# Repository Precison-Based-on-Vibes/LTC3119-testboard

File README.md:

# LTC3119-testboard
LTC3119 testbord is a device build to test MPPT adaptation of this DCDC converter

## Schematic

## Tests Documentation

### Configuration A
- Configuration of a testbed before tests:
    - Input Capacitance: 4 x 22 uF
    - Output Capacitance: 4 x 22uF
    - MPPC Compensation: 10nF, 1k47 Ohm (C5, R5)
    - Evrything else: same as in design files

- Nominal operation - Output noice mesurment (probed directly with coaxial cable with 50 ohm terminantion on oscilosope)
    - No external load (PSU not current limited)  
    
    - External load 1A (PSU not current limited)  
    
    - External load 2A (PSU not current limited)  
    
    - External load 3A (PSU not current limited)  

- MPPC Test - Output Voltage and noice mesurment (probed directly with coaxial cable with 50 ohm terminantion on oscilosope)
    - External load 1A - Messured output voltage - 4.09 V (voltage messured on electronic load, not compensated for voltage drop on cables) (PSU limited to 1A - not active)  
    
    - External load 1A5 - Messured output voltage - 3.13 V (voltage messured on electronic load, not compensated for voltage drop on cables) (PSU limited to 1A - active)   
    
    - External load 2A - Messured output voltage - 2.25 V (voltage messured on electronic load, not compensated for voltage drop on cables) (PSU limited to 1A - active)  
    
    - External load 1A3 - Messured output voltage - 3.63 V (voltage messured on electronic load, not compensated for voltage drop on cables) (PSU limited to 1A - active) (IMPORTANT: FFT for low frequency noice)

- MPPC Input voltage regulation setpoint vs control voltage  

### Configuration B
- Configuration of a tesbed before test:    
    - Input Capacitance: 4 x 22 uF
    - Output Capacitance: 4 x 22uF
    - MPPC Set point Components: 226k Ohm, 1M25 Ohm, 470k Ohm (R3, R2, R6)
    - MPPC Compensation: 2.2nF, 6k8 Ohm (C5, R5)
    - Evrything else: same as in design files

-  MPPC Test - Noice mesurment (probed directly with coaxial cable with 50 ohm terminantion on oscilosope)
   - External load 1A (PSU limited to 1A - not active)  
    
    - External load 1A5 (PSU limited to 1A - active)   
    
    - External load 2A (PSU limited to 1A - active)  
    
    - External load 1A3 - Messured output voltage - 3.63 V (PSU limited to 1A - active) (IMPORTANT: FFT for low frequency noice)

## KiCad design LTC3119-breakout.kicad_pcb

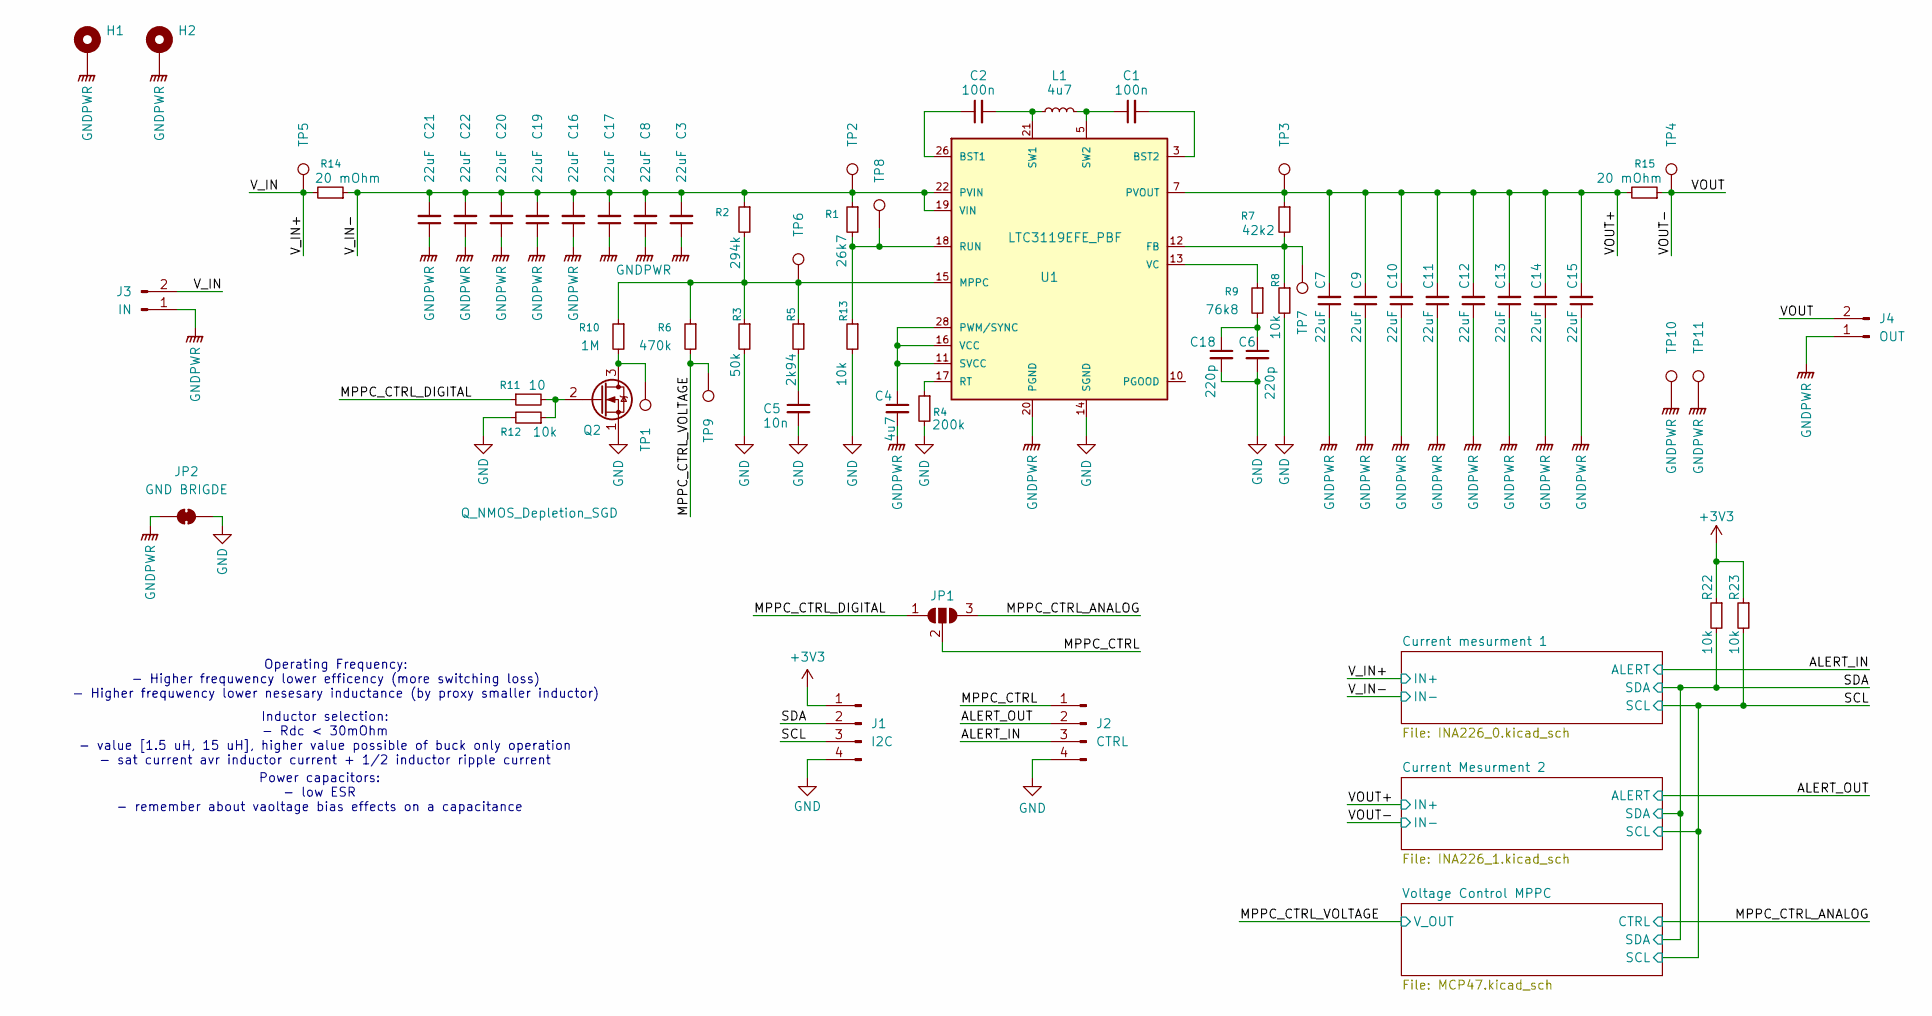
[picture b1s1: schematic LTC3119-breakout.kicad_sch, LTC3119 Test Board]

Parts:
C1, C2: 100n; C_0805_2012Metric_Pad1.18x1.45mm_HandSolder
C3, C7, C8, C9, C10, C11, C12, C13, C14, C15, C16, C17, C19, C20, C21, C22: 22uF; C_1210_3225Metric_Pad1.33x2.70mm_HandSolder
C4: 4u7; C_0805_2012Metric_Pad1.18x1.45mm_HandSolder
C5: 10n; C_0805_2012Metric_Pad1.18x1.45mm_HandSolder
C6, C18: 220p; C_0805_2012Metric_Pad1.18x1.45mm_HandSolder
H1, H2: MountingHole_Pad; MountingHole_3.2mm_M3_DIN965_Pad
J1: I2C; PinHeader_1x04_P2.54mm_Vertical
J2: CTRL; PinHeader_1x04_P2.54mm_Vertical
J3: IN; Molex_Pico-Lock_205338-0002_1x02-1MP_P2.00mm_Horizontal
J4: OUT; Molex_Pico-Lock_205338-0002_1x02-1MP_P2.00mm_Horizontal
JP1: SolderJumper_3_Open; SolderJumper-3_P1.3mm_Open_Pad1.0x1.5mm
JP2: GND BRIGDE; SolderJumper-2_P1.3mm_Bridged_Pad1.0x1.5mm
L1: 4u7; SRR1280A101M
Q2: Q_NMOS_Depletion_SGD; SOT-23_Handsoldering
R1: 26k7; R_0805_2012Metric_Pad1.20x1.40mm_HandSolder
R2: 294k; R_0805_2012Metric_Pad1.20x1.40mm_HandSolder
R3: 50k; R_0805_2012Metric_Pad1.20x1.40mm_HandSolder
R4: 200k; R_0805_2012Metric_Pad1.20x1.40mm_HandSolder
R5: 2k94; R_0805_2012Metric_Pad1.20x1.40mm_HandSolder
R6: 470k; R_0805_2012Metric_Pad1.20x1.40mm_HandSolder
R7: 42k2; R_0805_2012Metric_Pad1.20x1.40mm_HandSolder
R8, R12, R13, R22, R23: 10k; R_0805_2012Metric_Pad1.20x1.40mm_HandSolder
R9: 76k8; R_0805_2012Metric_Pad1.20x1.40mm_HandSolder
R10: 1M; R_0805_2012Metric_Pad1.20x1.40mm_HandSolder
R11: 10; R_0805_2012Metric_Pad1.20x1.40mm_HandSolder
R14, R15: 20 mOhm; R_0805_2012Metric_Pad1.20x1.40mm_HandSolder
TP1, TP2, TP3, TP4, TP5, TP6, TP7, TP8, TP9, TP10, TP11: TestPoint; TestPoint_Pad_D1.0mm
U1: LTC3119EFE_PBF; SOP65P640X120-29N; PARTREV B

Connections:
+3V3: J1.1, R22.1, R23.1; also elsewhere on the board
/ALERT_IN: J2.3; also elsewhere on the board
/ALERT_OUT: J2.2; also elsewhere on the board
/MPPC_CTRL: J2.1, JP1.2 (C)
/MPPC_CTRL_ANALOG: JP1.3 (B); also elsewhere on the board
/MPPC_CTRL_DIGITAL: JP1.1 (A), R11.1
/MPPC_CTRL_VOLTAGE: R6.2, TP9.1; also elsewhere on the board
/SCL: J1.3, R23.2; also elsewhere on the board
/SDA: J1.2, R22.2; also elsewhere on the board
/VOUT: J4.2, R15.1, TP4.1; also elsewhere on the board
/VOUT+: C7.2, C9.2, C10.2, C11.2, C12.2, C13.2, C14.2, C15.2, R7.1, R15.2, TP3.1, U1.6 (PVOUT), U1.7 (PVOUT); also elsewhere on the board
/V_IN: J3.2, R14.2, TP5.1; also elsewhere on the board
/V_IN-: C3.2, C8.2, C16.2, C17.2, C19.2, C20.2, C21.2, C22.2, R1.1, R2.1, R14.1, TP2.1, U1.19 (VIN), U1.22 (PVIN), U1.23 (PVIN); also elsewhere on the board
GND: C5.2, C6.2, C18.2, J1.4, J2.4, JP2.2 (B), Q2.1 (S), R3.2, R4.2, R8.2, R12.2, R13.2, U1.14 (SGND); also elsewhere on the board
GNDPWR: C3.1, C4.2, C7.1, C8.1, C9.1, C10.1, C11.1, C12.1, C13.1, C14.1, C15.1, C16.1, C17.1, C19.1, C20.1, C21.1, C22.1, H1.1, H2.1, J3.1, J4.1, JP2.1 (A), TP10.1, TP11.1, U1.4 (PGND), U1.9 (PGND), U1.20 (PGND), U1.25 (PGND), U1.29 (PGND)
unnamed: C1.1, L1.2, U1.5 (SW2), U1.8 (SW2)
unnamed: C2.2, L1.1, U1.21 (SW1), U1.24 (SW1)
unnamed: C5.1, R5.2
unnamed: C6.1, C18.1, R9.2
unnamed: Q2.3 (D), R10.2, TP1.1
unnamed: Q2.2 (G), R11.2, R12.1
unnamed: C2.1, U1.26 (BST1)
unnamed: C1.2, U1.3 (BST2)
unnamed: R7.2, R8.1, TP7.1, U1.12 (FB)
unnamed: R2.2, R3.1, R5.1, R6.1, R10.1, TP6.1, U1.15 (MPPC)
unnamed: C4.1, U1.11 (SVCC), U1.16 (VCC), U1.28 (PWM/SYNC)
unnamed: R4.1, U1.17 (RT)
unnamed: R1.2, R13.1, TP8.1, U1.18 (RUN)
unnamed: R9.1, U1.13 (VC)

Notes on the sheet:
Power capacitors: - low ESR - remember about vaoltage bias effects on a capacitance
Operating Frequency: - Higher frequwency lower efficency (more switching loss) - Higher frequwency lower nesesary inductance (by proxy smaller inductor)
Inductor selection: - Rdc < 30mOhm - value [1.5 uH, 15 uH], higher value possible of buck only operation - sat current avr inductor current + 1/2 inductor ripple current

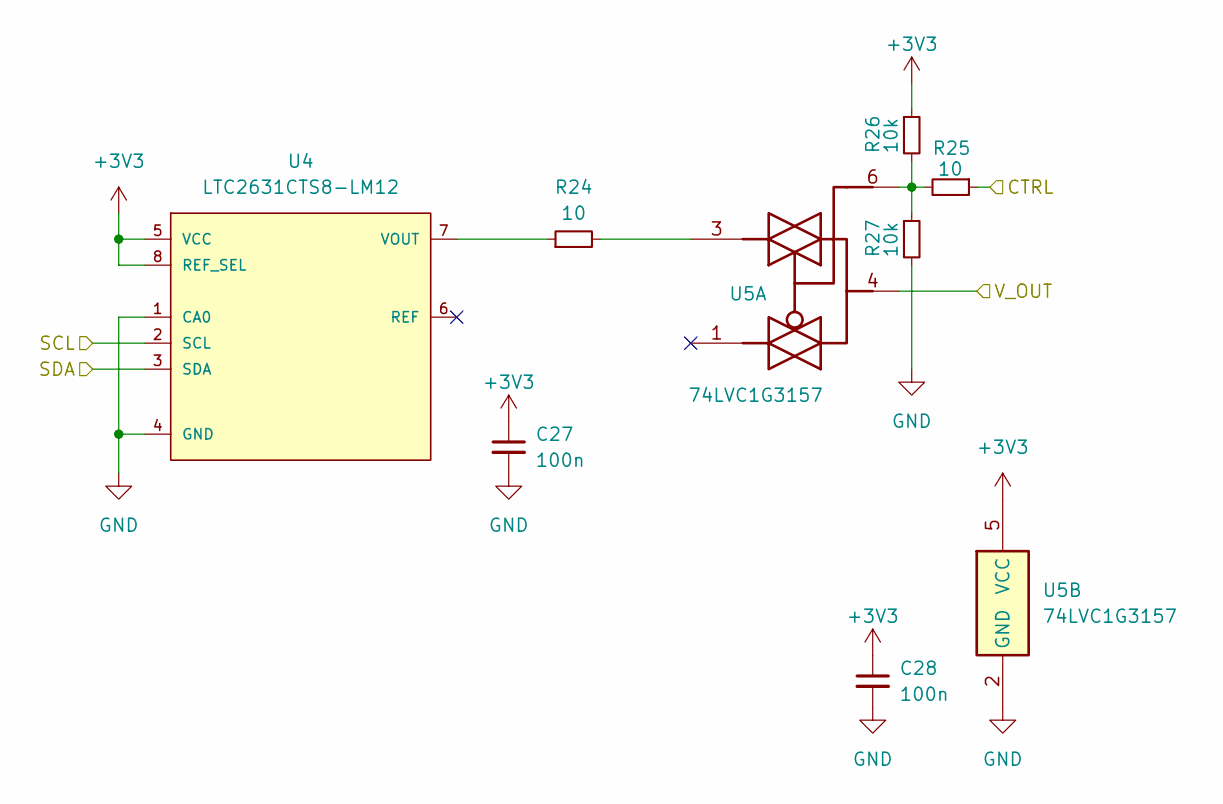
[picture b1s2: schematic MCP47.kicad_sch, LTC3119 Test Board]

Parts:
C27, C28: 100n; C_0805_2012Metric_Pad1.18x1.45mm_HandSolder
R24, R25: 10; R_0805_2012Metric_Pad1.20x1.40mm_HandSolder
R26, R27: 10k; R_0805_2012Metric_Pad1.20x1.40mm_HandSolder
U4: LTC2631CTS8-LM12; TSOT-23-8_HandSoldering
U5: 74LVC1G3157; SOT-23-6_Handsoldering

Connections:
+3V3: C27.1, C28.1, R26.1, U4.5 (VCC), U4.8 (REF_SEL), U5.5 (VCC); also elsewhere on the board
/MPPC_CTRL_ANALOG: R25.1; also elsewhere on the board
/MPPC_CTRL_VOLTAGE: U5.4; also elsewhere on the board
/SCL: U4.2 (SCL); also elsewhere on the board
/SDA: U4.3 (SDA); also elsewhere on the board
GND: C27.2, C28.2, R27.2, U4.1 (CA0), U4.4 (GND), U5.2 (GND); also elsewhere on the board
unnamed: R24.2, U5.3
unnamed: R25.2, R26.2, R27.1, U5.6
unnamed: R24.1, U4.7 (VOUT)

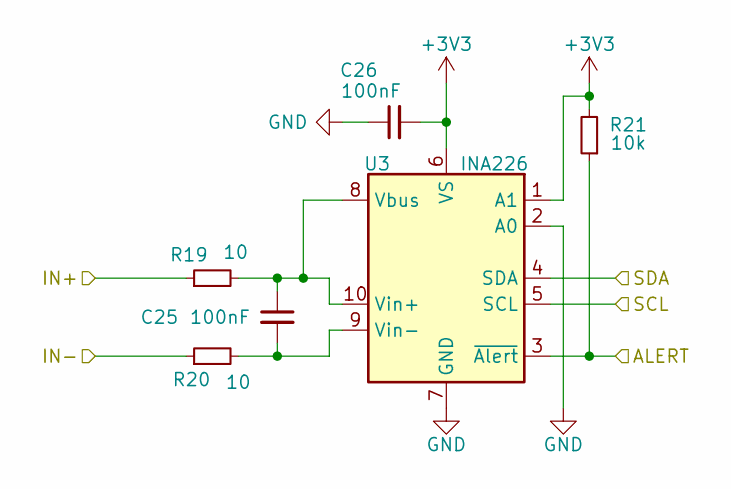
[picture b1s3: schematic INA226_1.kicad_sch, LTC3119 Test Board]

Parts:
C25, C26: 100nF; C_0805_2012Metric_Pad1.18x1.45mm_HandSolder
R19, R20: 10; R_0805_2012Metric_Pad1.20x1.40mm_HandSolder
R21: 10k; R_0805_2012Metric_Pad1.20x1.40mm_HandSolder
U3: INA226; VSSOP-10_3x3mm_P0.5mm

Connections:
+3V3: C26.2, R21.2, U3.1 (A1), U3.6 (VS); also elsewhere on the board
/ALERT_OUT: R21.1, U3.3 (~Alert); also elsewhere on the board
/SCL: U3.5 (SCL); also elsewhere on the board
/SDA: U3.4 (SDA); also elsewhere on the board
/VOUT: R20.1; also elsewhere on the board
/VOUT+: R19.1; also elsewhere on the board
GND: C26.1, U3.2 (A0), U3.7 (GND); also elsewhere on the board
unnamed: C25.1, R19.2, U3.8 (Vbus), U3.10 (Vin+)
unnamed: C25.2, R20.2, U3.9 (Vin-)

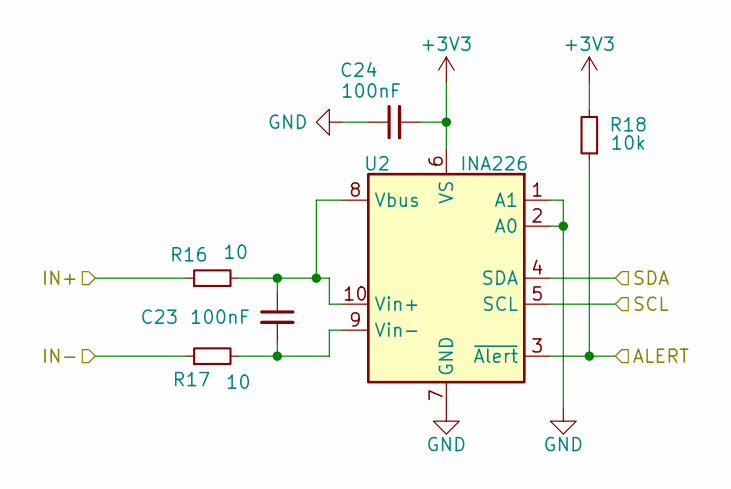
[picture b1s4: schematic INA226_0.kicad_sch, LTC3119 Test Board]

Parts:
C23, C24: 100nF; C_0805_2012Metric_Pad1.18x1.45mm_HandSolder
R16, R17: 10; R_0805_2012Metric_Pad1.20x1.40mm_HandSolder
R18: 10k; R_0805_2012Metric_Pad1.20x1.40mm_HandSolder
U2: INA226; VSSOP-10_3x3mm_P0.5mm

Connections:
+3V3: C24.2, R18.2, U2.6 (VS); also elsewhere on the board
/ALERT_IN: R18.1, U2.3 (~Alert); also elsewhere on the board
/SCL: U2.5 (SCL); also elsewhere on the board
/SDA: U2.4 (SDA); also elsewhere on the board
/V_IN: R16.1; also elsewhere on the board
/V_IN-: R17.1; also elsewhere on the board
GND: C24.1, U2.1 (A1), U2.2 (A0), U2.7 (GND); also elsewhere on the board
unnamed: C23.1, R16.2, U2.8 (Vbus), U2.10 (Vin+)
unnamed: C23.2, R17.2, U2.9 (Vin-)

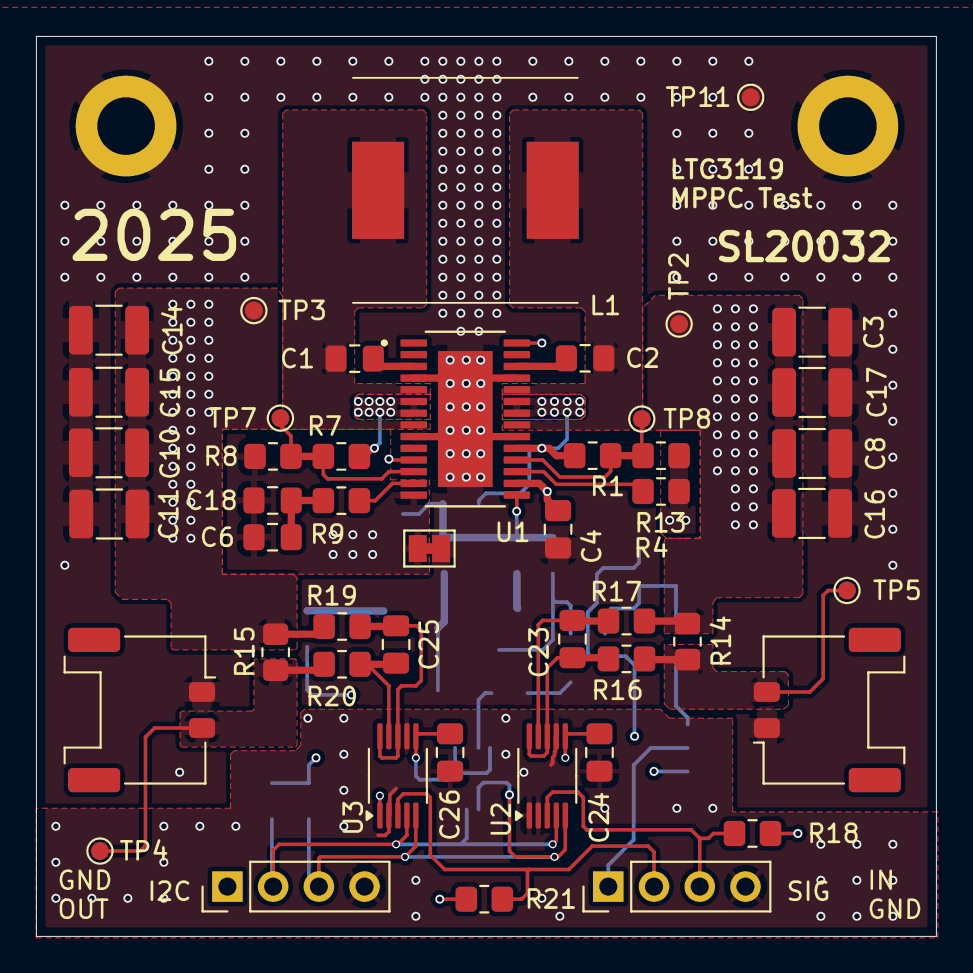
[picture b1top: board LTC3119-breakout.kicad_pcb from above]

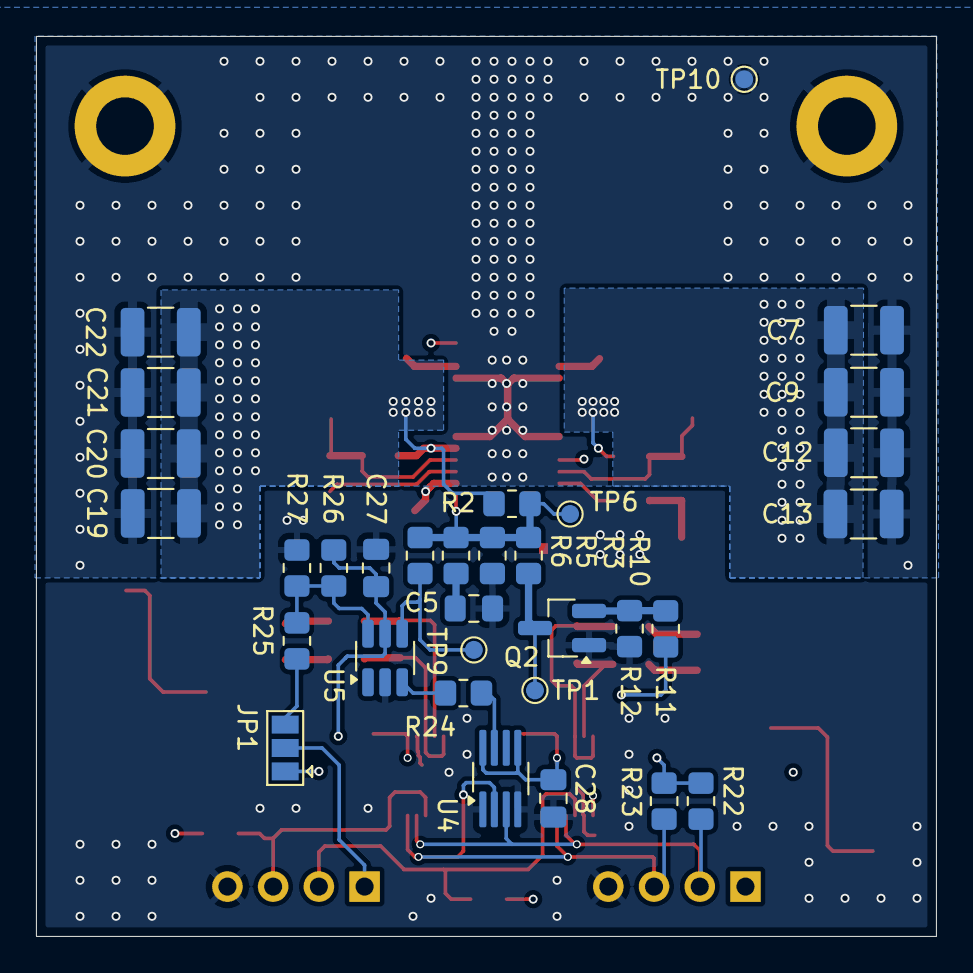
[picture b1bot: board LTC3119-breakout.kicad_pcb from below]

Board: 4 copper layers, 50.0 x 50.0 mm, 81 parts (32 on the bottom side), 36 nets.

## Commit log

2025-05-02 Clean Up production files
2025-05-02 Create LICENSE
2025-07-24 Update README with test data
